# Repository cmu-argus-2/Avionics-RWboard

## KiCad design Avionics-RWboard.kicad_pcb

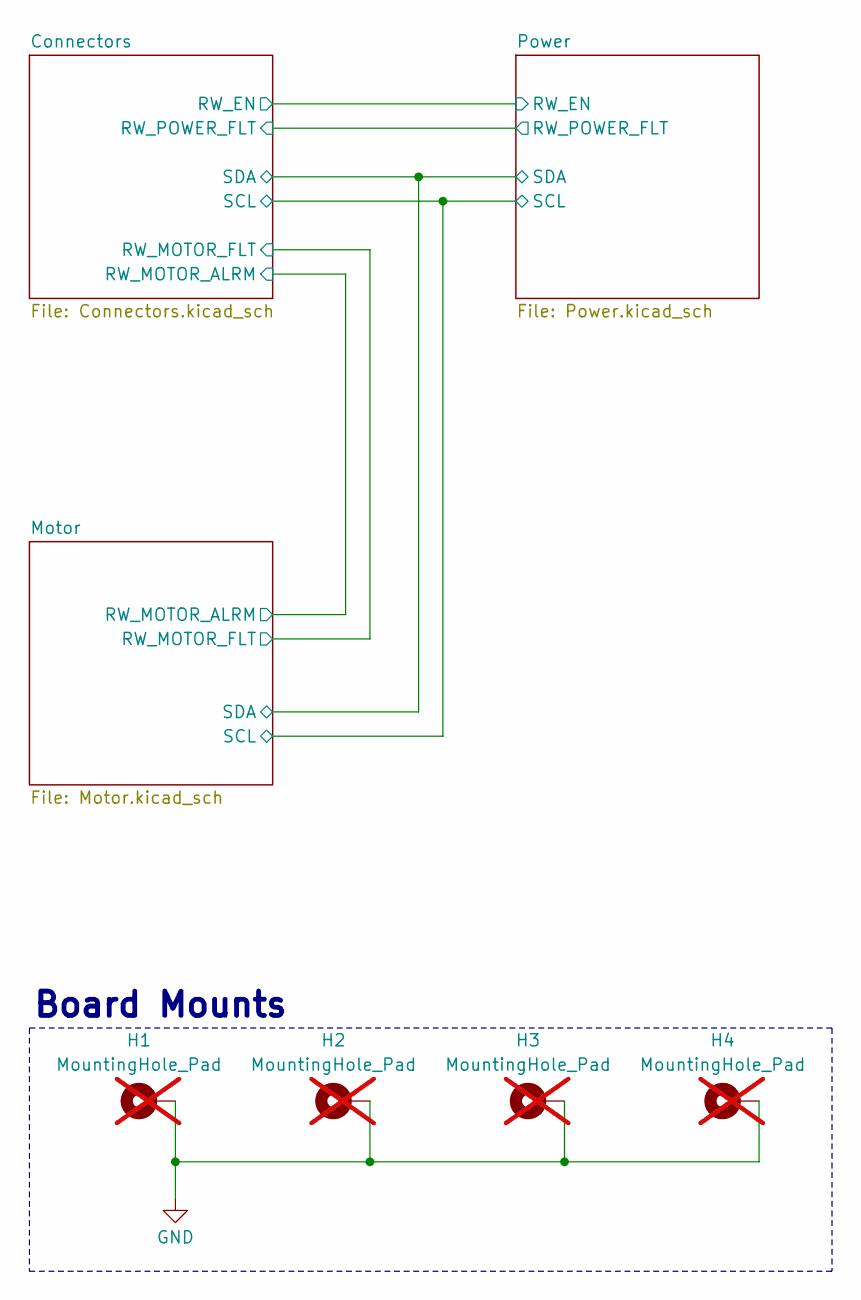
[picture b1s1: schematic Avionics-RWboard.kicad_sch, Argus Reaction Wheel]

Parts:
H1, H2, H3, H4: MountingHole_Pad; MountingHole_3.2mm_M3_Pad_Via; not fitted

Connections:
GND: H1.1, H2.1, H3.1, H4.1; also elsewhere on the board

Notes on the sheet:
Board Mounts

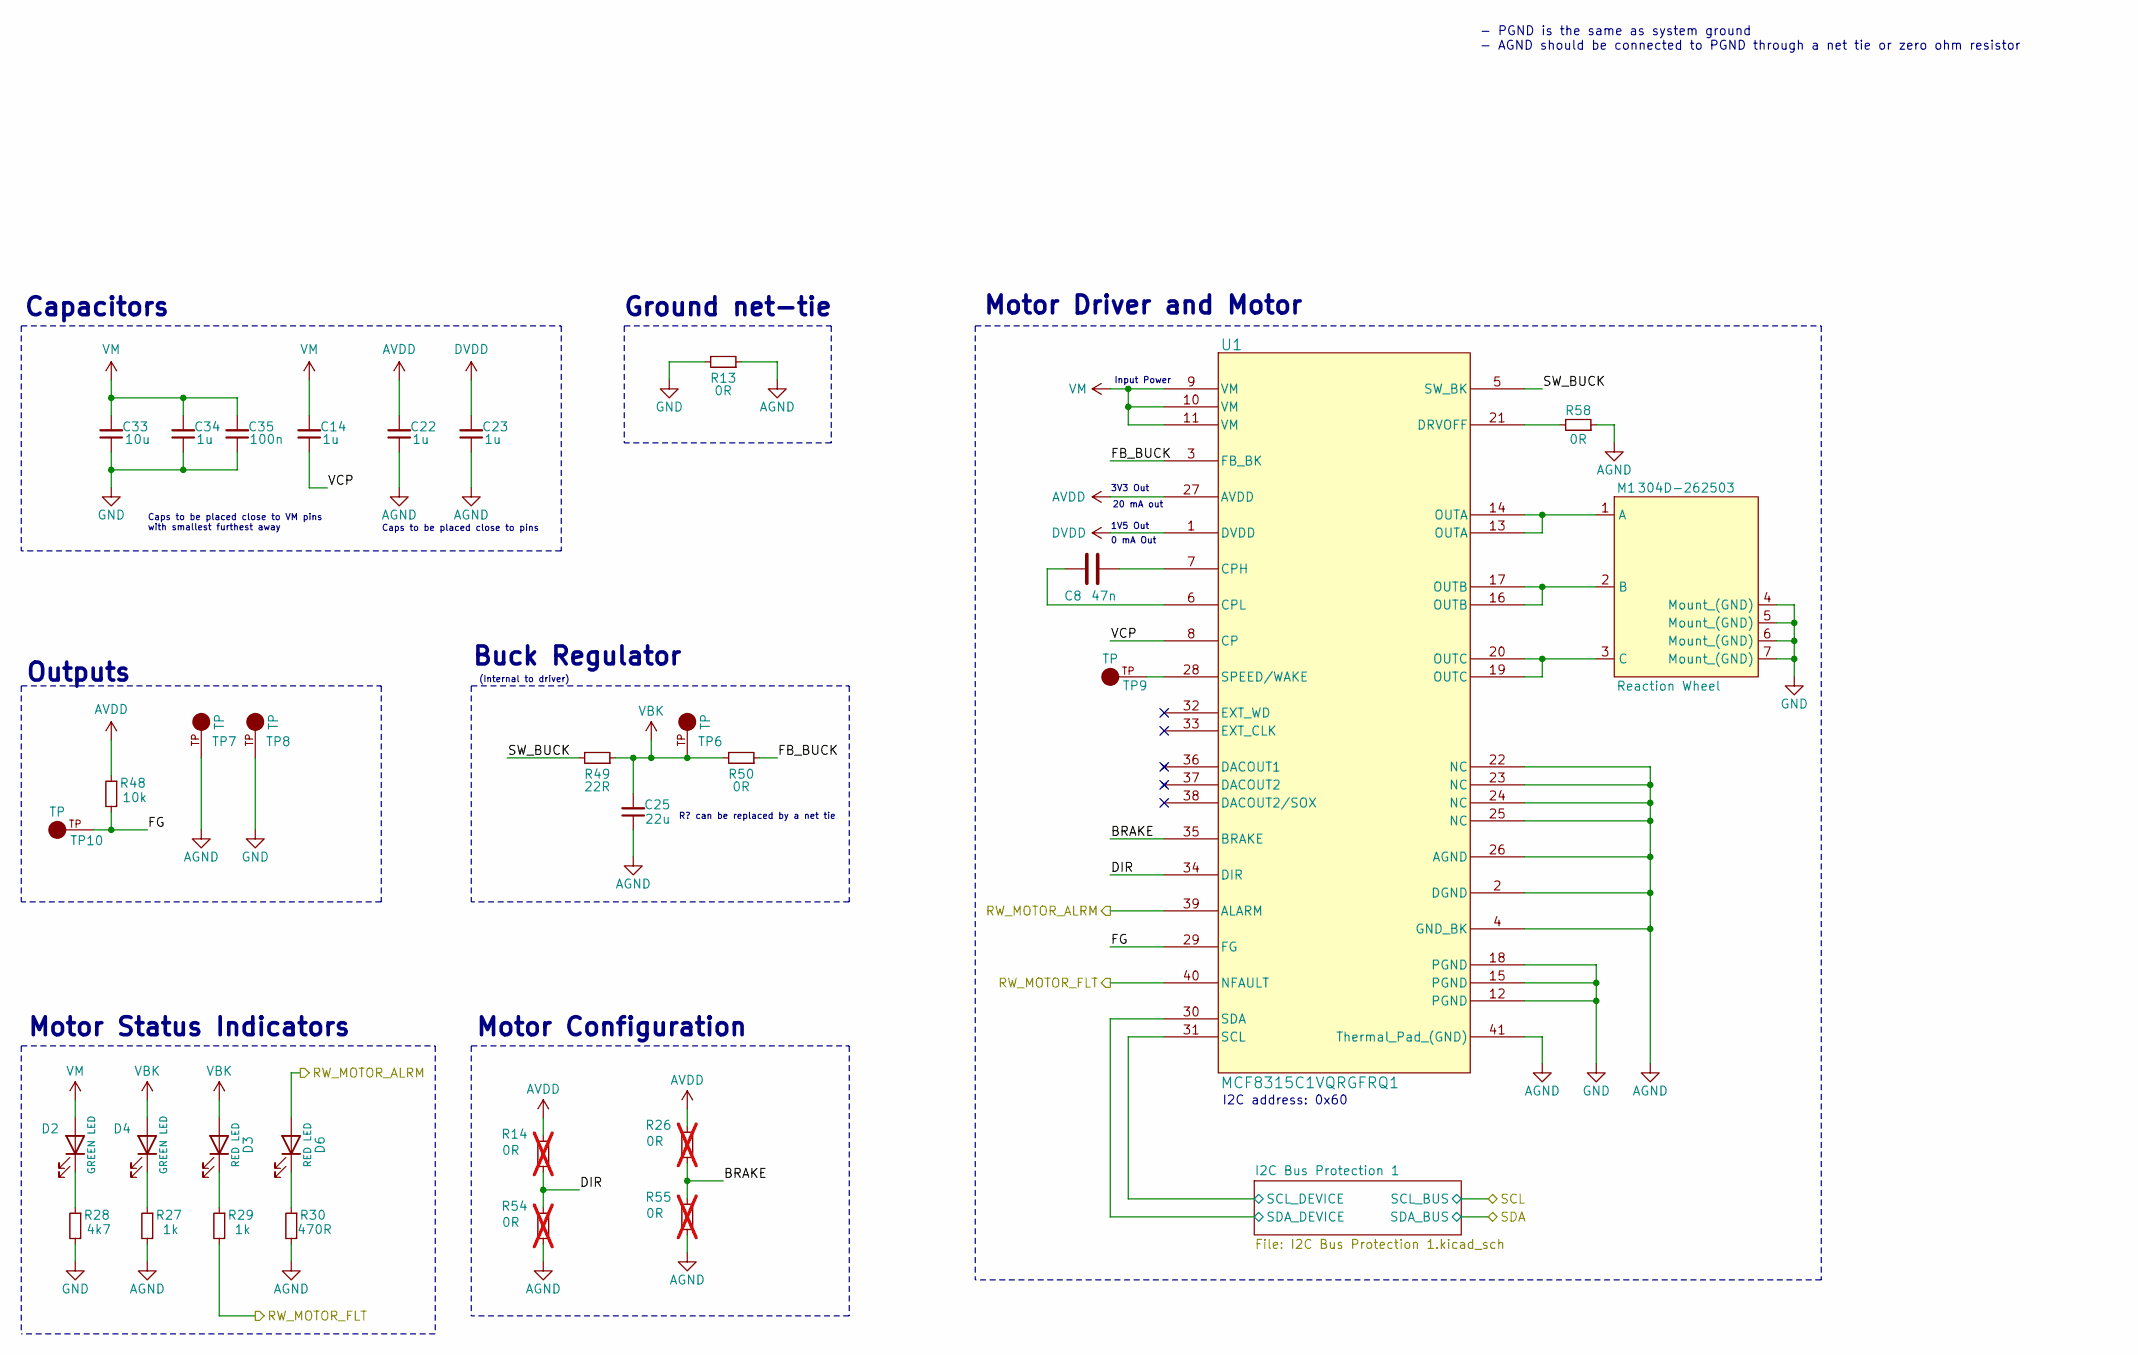
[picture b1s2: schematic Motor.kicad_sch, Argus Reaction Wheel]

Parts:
C8: 47n; C_0603_1608Metric; Part GCM188R71H473KA55D; Digikey PN 490-4934-1-ND
C14, C22, C23, C34: 1u; C_0603_1608Metric; Part CL10B105KA8NNNC; Digikey PN 1276-1184-1-ND
C25: 22u; C_0603_1608Metric; MPN CL10A226MP8NUNE; Digikey PN 1276-1274-1-ND
C33: 10u; C_1206_3216Metric_Pad1.33x1.80mm_HandSolder; Part CL31B106KAHNNNE; Digikey PN 1276-1804-1-ND
C35: 100n; C_0402_1005Metric_Pad0.74x0.62mm_HandSolder; Part C0402C103K3RACTU; Digikey PN 399-C0402C103K3RACTUCT-ND
D2, D4: GREEN LED; LED_0603_1608Metric; Manufacturer_Part_Number LTST-C190KGKT; Digikey PN 1830-1064-1-ND
D3, D6: RED LED; LED_0603_1608Metric; Manufacturer_Part_Number LTST-C190KRKT; Digikey PN 1830-1065-1-ND
M1: 304D-262503; Reaction_Wheel; MPN 304D-262503; Digikey PN 4827-304D-262503CT-ND
R13, R50: 0R; R_0805_2012Metric_Pad1.20x1.40mm_HandSolder; MPN RC0805JR-070RL; Digikey PN 311-0.0ARCT-ND
R14, R26, R54, R55: 0R; R_0402_1005Metric_Pad0.72x0.64mm_HandSolder; MPN RC0402JR-070RL; Digikey PN 311-0.0JRCT-ND; not fitted
R27, R29: 1k; R_0603_1608Metric; MPN RC0603FR-071KL; Digikey PN 311-1.00KHRCT-ND
R28: 4k7; R_0603_1608Metric; MPN RC0603FR-074K7L; Digikey PN 311-4.70KHRCT-ND
R30: 470R; R_0603_1608Metric; MPN RC0603FR-13470RL; Digikey PN 13-RC0603FR-13470RLCT-ND
R48: 10k; R_0603_1608Metric; MPN RC0603FR-0710KL; Digikey PN 311-10.0KHRCT-ND
R49: 22R; R_2512_6332Metric_Pad1.40x3.35mm_HandSolder; Part CRCW251222R0FKEGHP; Digikey PN 541-CRCW251222R0FKEGHPCT-ND
R58: 0R; R_0402_1005Metric_Pad0.72x0.64mm_HandSolder; MPN RC0402JR-070RL; Digikey PN 311-0.0JRCT-ND
TP6, TP7, TP8, TP9, TP10: TP; KEYSTONE_5001; MPN 5001; Digikey PN 36-5001-ND
U1: MCF8315C1VQRGFRQ1; VQFN40_RGF_TEX; MPN MCF8315C1VQRGFRQ1; Digikey PN 296-MCF8315C1VQRGFRQ1CT-ND

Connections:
/Connectors/RW_MOTOR_ALRM: D6.2 (A), U1.39 (ALARM); also elsewhere on the board
/Connectors/RW_MOTOR_FLT: R29.2, U1.40 (NFAULT); also elsewhere on the board
/Motor/BRAKE: R26.1, R55.2, U1.35 (BRAKE)
/Motor/DIR: R14.1, R54.2, U1.34 (DIR)
/Motor/FB_BUCK: R50.1, U1.3 (FB_BK)
/Motor/FG: R48.2, TP10.TP, U1.29 (FG)
/Motor/I2C Bus Protection 1/SCL_DEVICE: U1.31 (SCL); also elsewhere on the board
/Motor/I2C Bus Protection 1/SDA_DEVICE: U1.30 (SDA); also elsewhere on the board
/Motor/SW_BUCK: R49.2, U1.5 (SW_BK)
/Motor/VCP: C14.1, U1.8 (CP)
AGND: C22.1, C23.1, C25.1, R13.1, R27.2, R30.2, R54.1, R55.1, R58.1, TP7.TP, U1.2 (DGND), U1.4 (GND_BK), U1.22 (NC), U1.23 (NC), U1.24 (NC), U1.25 (NC), U1.26 (AGND), U1.41 (Thermal_Pad_(GND))
AVDD: C22.2, R14.2, R26.2, R48.1, U1.27 (AVDD)
DVDD: C23.2, U1.1 (DVDD)
GND: C33.1, C34.1, C35.1, M1.4 (Mount_(GND)), M1.5 (Mount_(GND)), M1.6 (Mount_(GND)), M1.7 (Mount_(GND)), R13.2, R28.2, TP8.TP, U1.12 (PGND), U1.15 (PGND), U1.18 (PGND); also elsewhere on the board
unnamed: D2.1 (K), R28.1
unnamed: D3.1 (K), R29.1
unnamed: D4.1 (K), R27.1
unnamed: D6.1 (K), R30.1
unnamed: M1.1 (A), U1.13 (OUTA), U1.14 (OUTA)
unnamed: M1.2 (B), U1.16 (OUTB), U1.17 (OUTB)
unnamed: M1.3 (C), U1.19 (OUTC), U1.20 (OUTC)
unnamed: C8.1, U1.7 (CPH)
unnamed: C8.2, U1.6 (CPL)
unnamed: R58.2, U1.21 (DRVOFF)
unnamed: TP9.TP, U1.28 (SPEED/WAKE)
VBK: C25.2, D3.2 (A), D4.2 (A), R49.1, R50.2, TP6.TP
VM: C14.2, C33.2, C34.2, C35.2, D2.2 (A), U1.9 (VM), U1.10 (VM), U1.11 (VM); also elsewhere on the board

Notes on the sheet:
20 mA out
3V3 Out
Caps to be placed close to pins
Buck Regulator
0 mA Out
R? can be replaced by a net tie
Input Power
Motor Status Indicators
I2C address: 0x60
Motor Driver and Motor
Caps to be placed close to VM pins with smallest furthest away
Ground net-tie
Outputs
1V5 Out
- PGND is the same as system ground - AGND should be connected to PGND through a net tie or zero ohm resistor
Motor Configuration
(Internal to driver)
Capacitors

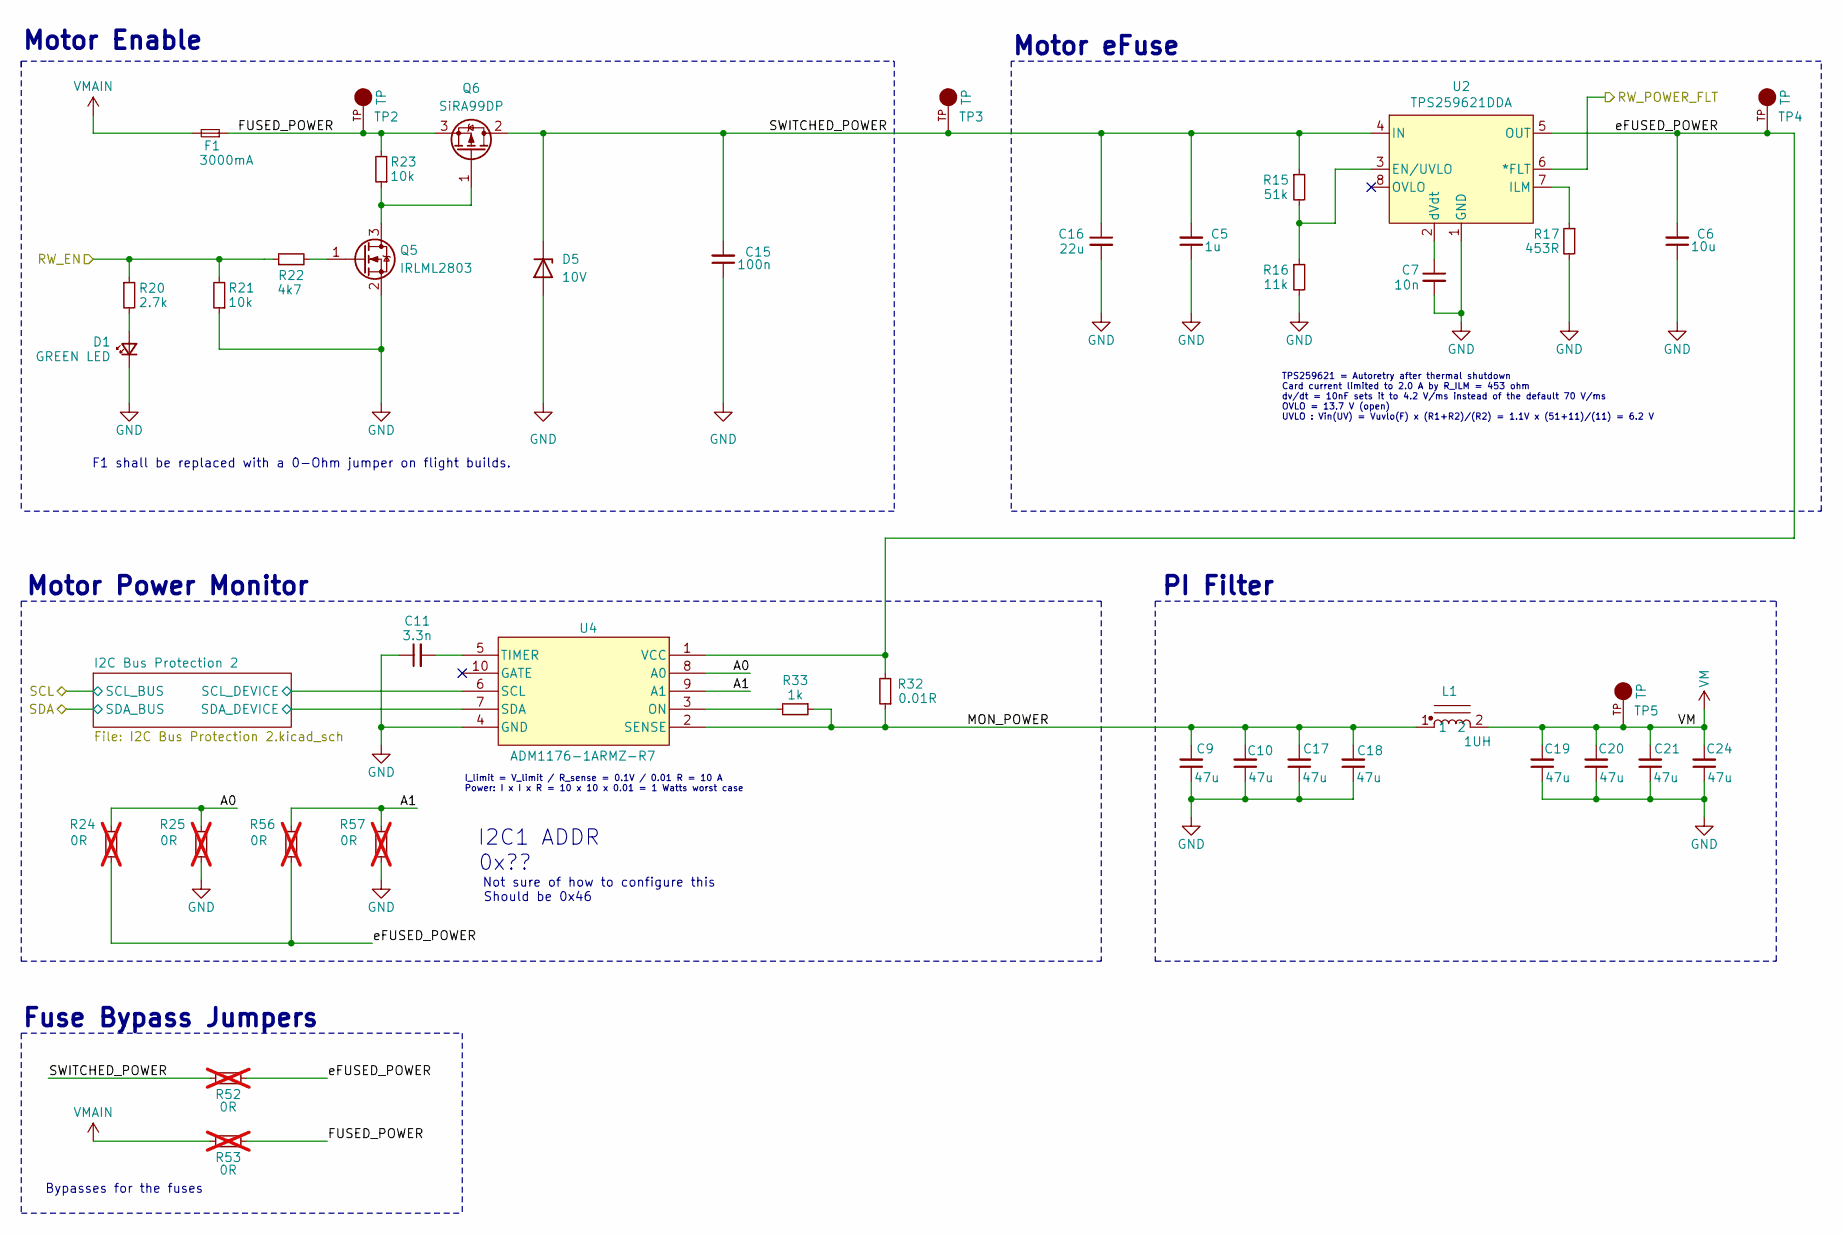
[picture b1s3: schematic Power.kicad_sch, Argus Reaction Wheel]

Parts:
C5: 1u; C_0603_1608Metric; Part CL10B105KA8NNNC; Digikey PN 1276-1184-1-ND
C6: 10u; C_1206_3216Metric_Pad1.33x1.80mm_HandSolder; Part CL31B106KAHNNNE; Digikey PN 1276-1804-1-ND
C7: 10n; C_0603_1608Metric; MPN CL10B103KO8WPNC; Digikey PN 490-4934-1-ND
C9, C10, C17, C18, C19, C20, C21, C24: 47u; C_1206_3216Metric_Pad1.33x1.80mm_HandSolder; Part C3216X5R1E476M160AC; Digikey PN 445-8047-1-ND
C11: 3.3n; C_0603_1608Metric; Part C0603C332K4REC7411; Digikey PN 399-C0603C332K4REC7411CT-ND
C15: 100n; C_0402_1005Metric_Pad0.74x0.62mm_HandSolder; Part C0402C103K3RACTU; Digikey PN 399-C0402C103K3RACTUCT-ND
C16: 22u; C_1210_3225Metric_Pad1.33x2.70mm_HandSolder; MPN GCM32EC71E226KE36K; Digikey PN 490-GCM32EC71E226KE36KCT-ND
D1: GREEN LED; LED_0603_1608Metric; MPN IN-S63AT5A; Digikey PN 1830-1064-1-ND
D5: 10V; Nexperia_DSN1608-2_1.6x0.8mm; MPN PTVS10VZ1USKYL; Digikey PN 1727-2744-1-ND
F1: 3000mA; Fuse_0603_1608Metric; Part SF-0603S300-2; Digikey PN SF-0603S300-2CT-ND
L1: 1UH; HCM1A1104V2; Part HCM1A1104V2-1R0-R; Digikey PN 283-HCM1A1104V2-1R0-RCT-ND
Q5: IRLML2803; SOT-23; MPN IRLML2803TRPBF; Digikey PN IRLML2803PBFCT-ND
Q6: SiRA99DP; PowerPAK SO-8; MPN SIRA99DP-T1-GE3; Digikey PN SIRA99DP-T1-GE3CT-ND
R15: 51k; R_0603_1608Metric; MPN RC0603FR-0751KL; Digikey PN 311-51.0KHRCT-ND
R16: 11k; R_0603_1608Metric; MPN RC0603FR-0711KL; Digikey PN 311-11.0KHRCT-ND
R17: 453R; R_0603_1608Metric; MPN RC0603FR-07453RL; Digikey PN 311-453HRCT-ND
R20: 2.7k; R_0603_1608Metric; MPN CRGCQ0603F2K7; Digikey PN A129693CT-ND
R21, R23: 10k; R_0603_1608Metric; MPN RC0603FR-0710KL; Digikey PN 311-10.0KHRCT-ND
R22: 4k7; R_0603_1608Metric; MPN RC0603FR-074K7L; Digikey PN 311-4.70KHRCT-ND
R24, R25, R56, R57: 0R; R_0402_1005Metric_Pad0.72x0.64mm_HandSolder; MPN RC0402JR-070RL; Digikey PN 311-0.0JRCT-ND; not fitted
R32: 0.01R; R_0805_2012Metric_Pad1.20x1.40mm_HandSolder; Part ERJ-8BWFR010V; Digikey PN P.010AUCT-ND
R33: 1k; R_0603_1608Metric; MPN RC0603FR-071KL; Digikey PN 311-1.00KHRCT-ND
R52, R53: 0R; R_2512_6332Metric_Pad1.40x3.35mm_HandSolder; Part RC2512FK-070RL; Digikey PN 13-RC2512FK-070RLCT-ND; not fitted
TP2, TP3, TP4, TP5: TP; KEYSTONE_5001; MPN 5001; Digikey PN 36-5001-ND
U2: TPS259621DDA; Texas_R-PDSO-G8_EP2.95x4.9mm_Mask2.4x3.1mm_ThermalVias; MPN TPS259620DDAT; Digikey PN 296-TPS259621DDARCT-ND
U4: ADM1176-1ARMZ-R7; MSOP-10_3x3mm_P0.5mm; Manufacturer_Part_Number ADM1176-1ARMZ-R7; Digikey PN 505-ADM1176-1ARMZ-R7CT-ND

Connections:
/Connectors/RW_EN: R20.1, R21.2, R22.1; also elsewhere on the board
/Connectors/RW_POWER_FLT: U2.6 (*FLT); also elsewhere on the board
/Power/A0: R24.2, R25.2, U4.8 (A0)
/Power/A1: R56.2, R57.2, U4.9 (A1)
/Power/FUSED_POWER: F1.1, Q6.3 (S), R23.2, R53.1, TP2.TP
/Power/I2C Bus Protection 2/SCL_DEVICE: U4.6 (SCL); also elsewhere on the board
/Power/I2C Bus Protection 2/SDA_DEVICE: U4.7 (SDA); also elsewhere on the board
/Power/MON_POWER: C9.2, C10.2, C17.2, C18.2, L1.1, R32.1, R33.1, U4.2 (SENSE)
/Power/SWITCHED_POWER: C5.2, C15.2, C16.1, D5.1 (K), Q6.2 (D), R15.1, R52.2, TP3.TP, U2.4 (IN)
/Power/eFUSED_POWER: C6.2, R24.1, R32.2, R52.1, R56.1, TP4.TP, U2.5 (OUT), U4.1 (VCC)
GND: C5.1, C6.1, C7.2, C9.1, C10.1, C11.1, C15.1, C16.2, C17.1, C18.1, C19.1, C20.1, C21.1, C24.1, D1.1 (K), D5.2 (A), Q5.2 (S), R16.2, R17.2, R21.1, R25.1, R57.1, U2.1 (GND), U2.9 (GND), U4.4 (GND); also elsewhere on the board
unnamed: D1.2 (A), R20.2
unnamed: Q5.3 (D), Q6.1 (G), R23.1
unnamed: Q5.1 (G), R22.2
unnamed: R15.2, R16.1, U2.3 (EN/UVLO)
unnamed: R17.1, U2.7 (ILM)
unnamed: C7.1, U2.2 (dVdt)
unnamed: R33.2, U4.3 (ON)
unnamed: C11.2, U4.5 (TIMER)
VM: C19.2, C20.2, C21.2, C24.2, L1.2, TP5.TP; also elsewhere on the board
VMAIN: F1.2, R53.2; also elsewhere on the board

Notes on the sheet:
Not sure of how to configure this
I2C1 ADDR
0x??
Motor Enable
F1 shall be replaced with a 0-Ohm jumper on flight builds.
I_limit = V_limit / R_sense = 0.1V / 0.01 R = 10 A Power: I x I x R = 10 x 10 x 0.01 = 1 Watts worst case
Motor Power Monitor
TPS259621 = Autoretry after thermal shutdown Card current limited to 2.0 A by R_ILM = 453 ohm dv/dt = 10nF sets it to 4.2 V/ms instead of the default 70 V/ms OVLO = 13.7 V (open) UVLO : Vin(UV) = Vuvlo(F) x (R1+R2)/(R2) = 1.1V x (51+11)/(11) = 6.2 V
Fuse Bypass Jumpers
Should be 0x46
PI Filter
Bypasses for the fuses
Motor eFuse

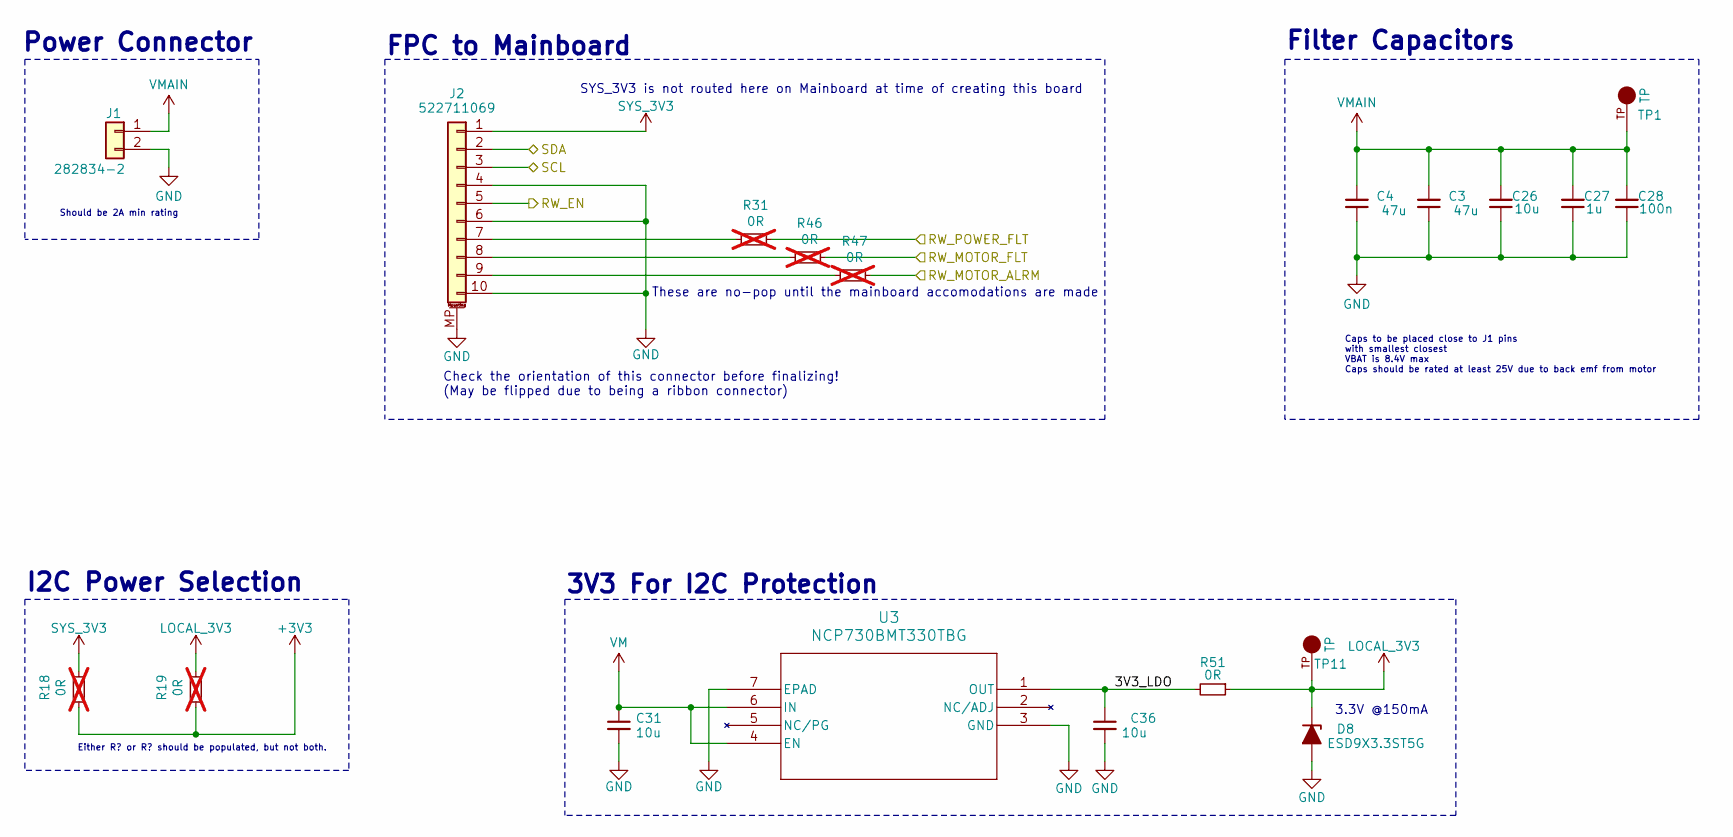
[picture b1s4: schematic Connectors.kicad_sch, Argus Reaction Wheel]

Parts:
C3, C4: 47u; C_1206_3216Metric_Pad1.33x1.80mm_HandSolder; Part C3216X5R1E476M160AC; Digikey PN 445-8047-1-ND
C26: 10u; C_1206_3216Metric_Pad1.33x1.80mm_HandSolder; Part CL31B106KAHNNNE; Digikey PN 1276-1804-1-ND
C27: 1u; C_0603_1608Metric; Part CL10B105KA8NNNC; Digikey PN 1276-1184-1-ND
C28: 100n; C_0402_1005Metric_Pad0.74x0.62mm_HandSolder; Part C0402C103K3RACTU; Digikey PN 399-C0402C103K3RACTUCT-ND
C31, C36: 10u; C_0603_1608Metric; MPN C1608X5R1E106M080AC; Digikey PN 445-9015-1-ND
D8: ESD9X3.3ST5G; D_SOD-923; MPN ESD9X5.0ST5G; Digikey PN ESD9X3.3ST5GOSCT-ND
J1: 282834-2; TE_282834-2; MPN 282834-2; Digikey PN A98333-ND
J2: 522711069; Molex_200528-0100_1x10-1MP_P1.00mm_Horizontal; MPN 200528-0100; Digikey PN 900-2005280100CT-ND
R18, R19, R31, R46, R47: 0R; R_0402_1005Metric_Pad0.72x0.64mm_HandSolder; MPN RC0402JR-070RL; Digikey PN 311-0.0JRCT-ND; not fitted
R51: 0R; R_0603_1608Metric; MPN CR0603-J/-000ELF; Digikey PN CR0603-J/-000ELFCT-ND
TP1, TP11: TP; KEYSTONE_5001; MPN 5001; Digikey PN 36-5001-ND
U3: NCP730BMT330TBG; WDFN6-2x2_511BR_OSI; MPN NCP730BMT330TBG; Digikey PN 488-NCP730BMT330TBGCT-ND

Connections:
+3V3: R18.1, R19.1; also elsewhere on the board
/Connectors/3V3_LDO: C36.1, R51.2, U3.1 (OUT)
/Connectors/RW_EN: J2.5; also elsewhere on the board
/Connectors/RW_MOTOR_ALRM: R47.2; also elsewhere on the board
/Connectors/RW_MOTOR_FLT: R46.2; also elsewhere on the board
/Connectors/RW_POWER_FLT: R31.2; also elsewhere on the board
/Connectors/SCL: J2.3; also elsewhere on the board
/Connectors/SDA: J2.2; also elsewhere on the board
GND: C3.1, C4.1, C26.1, C27.1, C28.1, C31.2, C36.2, D8.2 (A), J1.2, J2.4, J2.6, J2.10, J2.MP (MountPin), U3.3 (GND), U3.7 (EPAD); also elsewhere on the board
LOCAL_3V3: D8.1 (K), R19.2, R51.1, TP11.TP
unnamed: J2.7, R31.1
unnamed: J2.8, R46.1
unnamed: J2.9, R47.1
SYS_3V3: J2.1, R18.2
VM: C31.1, U3.4 (EN), U3.6 (IN); also elsewhere on the board
VMAIN: C3.2, C4.2, C26.2, C27.2, C28.2, J1.1, TP1.TP; also elsewhere on the board

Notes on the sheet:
Filter Capacitors
Caps to be placed close to J1 pins with smallest closest VBAT is 8.4V max Caps should be rated at least 25V due to back emf from motor
3.3V @150mA
These are no-pop until the mainboard accomodations are made
Check the orientation of this connector before finalizing! (May be flipped due to being a ribbon connector)
Either R? or R? should be populated, but not both.
3V3 For I2C Protection
Should be 2A min rating
I2C Power Selection
SYS_3V3 is not routed here on Mainboard at time of creating this board
Power Connector
FPC to Mainboard

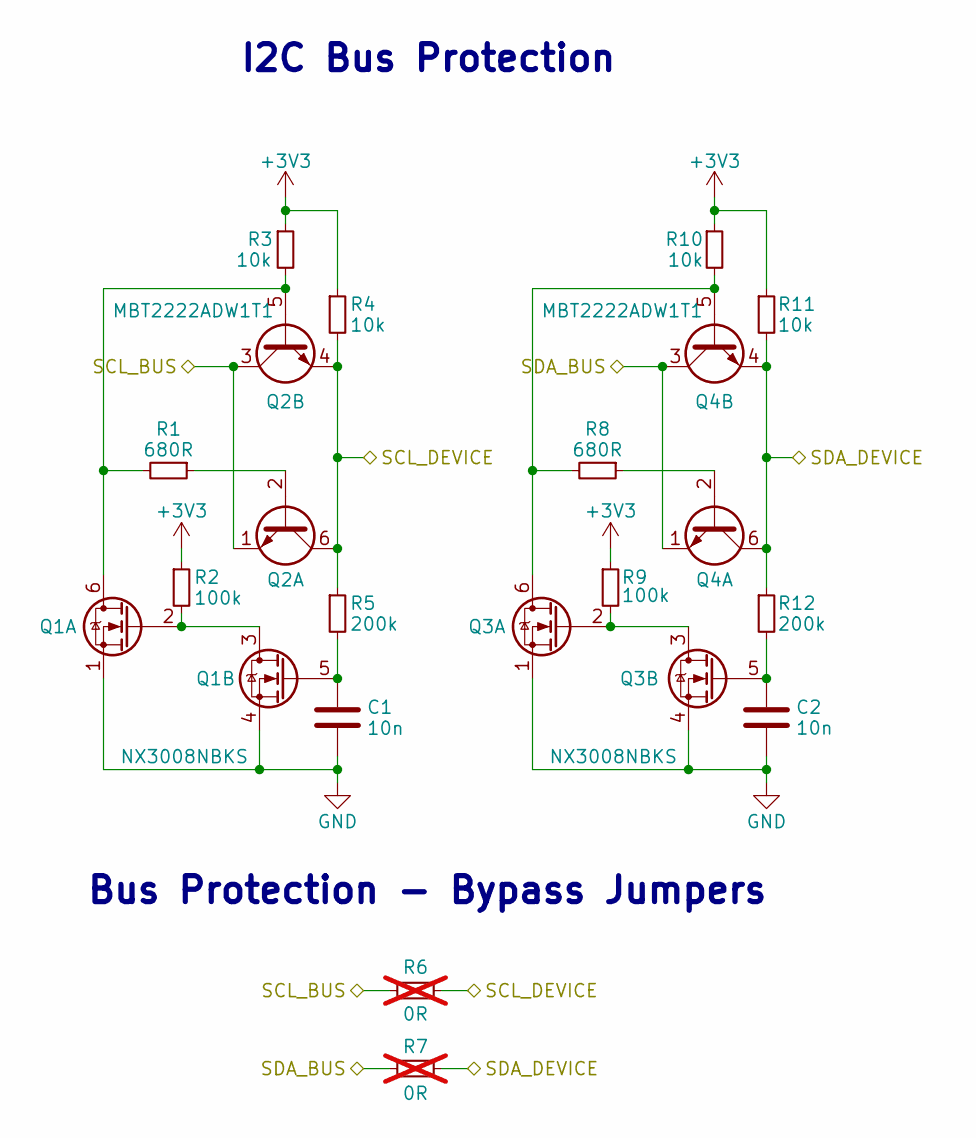
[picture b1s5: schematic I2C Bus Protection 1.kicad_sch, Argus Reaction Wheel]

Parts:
C1, C2: 10n; C_0603_1608Metric; Part CL10B103KO8WPNC; Digikey PN 490-4934-1-ND
Q1, Q3: NX3008NBKS; SOT-363_SC-70-6; Manufacturer_Part_Number NX3008NBKS; Digikey PN 1727-1221-1-ND
Q2, Q4: MBT2222ADW1T1; SOT-363_SC-70-6; Manufacturer_Part_Number MBT2222ADW1T1G; Digikey PN MBT2222ADW1T1GOSCT-ND
R1, R8: 680R; R_0603_1608Metric; MPN RC0603FR-07680RL; Digikey PN 311-680HRCT-ND
R2, R9: 100k; R_0603_1608Metric; MPN RC0603FR-07100KL; Digikey PN 311-100KHRCT-ND
R3, R4, R10, R11: 10k; R_0603_1608Metric; MPN RC0603FR-0710KL; Digikey PN 311-10.0KHRCT-ND
R5, R12: 200k; R_0603_1608Metric; MPN RC0603FR-07200KL; Digikey PN 311-200KHRCT-ND
R6, R7: 0R; R_0603_1608Metric; MPN CR0603-J/-000ELF; Digikey PN CR0603-J/-000ELFCT-ND; not fitted

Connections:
+3V3: R2.1, R3.1, R4.1, R9.1, R10.1, R11.1; also elsewhere on the board
/Connectors/SCL: Q2.1 (E1), Q2.3 (C2), R6.2; also elsewhere on the board
/Connectors/SDA: Q4.1 (E1), Q4.3 (C2), R7.2; also elsewhere on the board
/Motor/I2C Bus Protection 1/SCL_DEVICE: Q2.4 (E2), Q2.6 (C1), R4.2, R5.1, R6.1; also elsewhere on the board
/Motor/I2C Bus Protection 1/SDA_DEVICE: Q4.4 (E2), Q4.6 (C1), R7.1, R11.2, R12.1; also elsewhere on the board
GND: C1.2, C2.2, Q1.1 (S), Q1.4 (S), Q3.1 (S), Q3.4 (S); also elsewhere on the board
unnamed: Q1.6 (D), Q2.5 (B2), R1.2, R3.2
unnamed: Q1.2 (G), Q1.3 (D), R2.2
unnamed: C1.1, Q1.5 (G), R5.2
unnamed: Q2.2 (B1), R1.1
unnamed: Q3.6 (D), Q4.5 (B2), R8.2, R10.2
unnamed: Q3.2 (G), Q3.3 (D), R9.2
unnamed: C2.1, Q3.5 (G), R12.2
unnamed: Q4.2 (B1), R8.1

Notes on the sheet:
Bus Protection - Bypass Jumpers
I2C Bus Protection

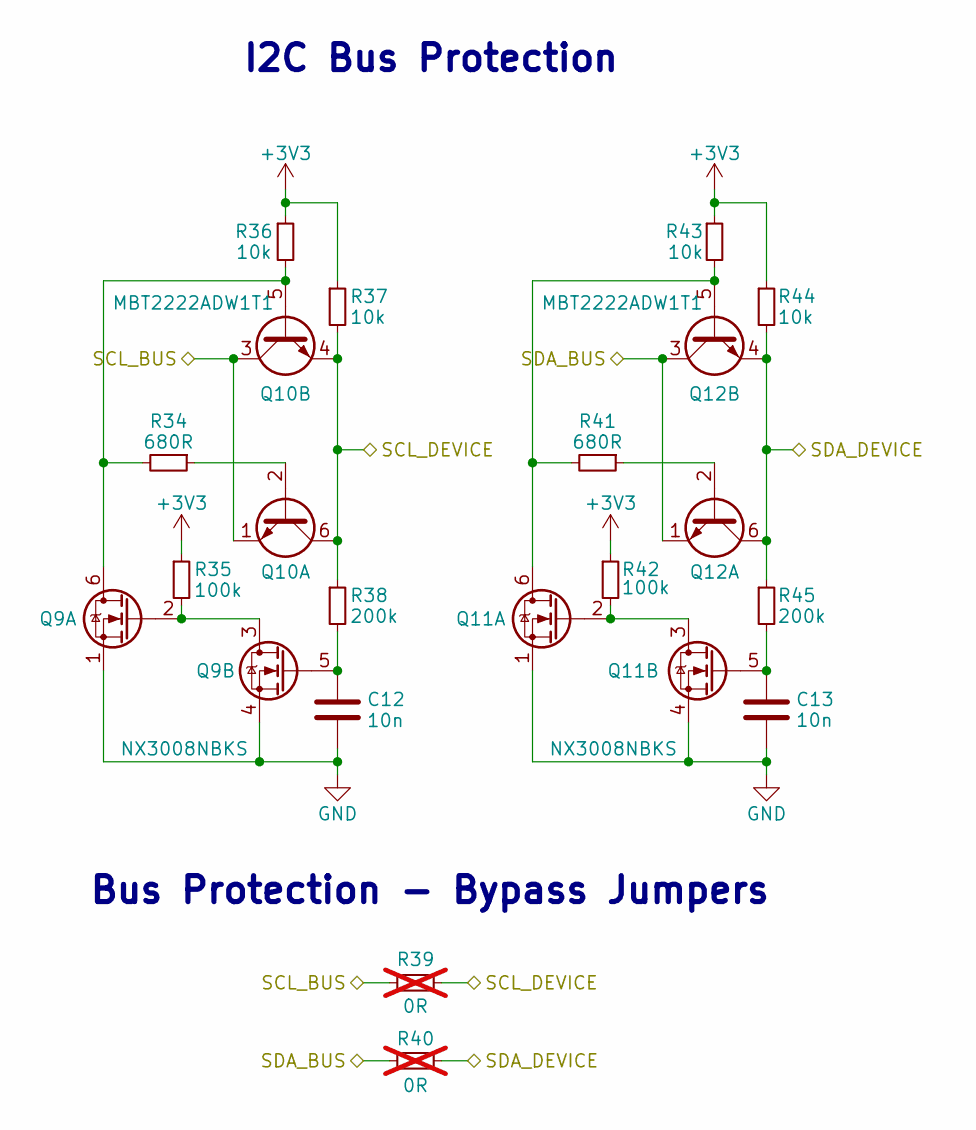
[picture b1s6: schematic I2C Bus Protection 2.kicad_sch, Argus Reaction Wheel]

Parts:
C12, C13: 10n; C_0603_1608Metric; Part CL10B103KO8WPNC; Digikey PN 490-4934-1-ND
Q9, Q11: NX3008NBKS; SOT-363_SC-70-6; Manufacturer_Part_Number NX3008NBKS; Digikey PN 1727-1221-1-ND
Q10, Q12: MBT2222ADW1T1; SOT-363_SC-70-6; Manufacturer_Part_Number MBT2222ADW1T1G; Digikey PN MBT2222ADW1T1GOSCT-ND
R34, R41: 680R; R_0603_1608Metric; MPN RC0603FR-07680RL; Digikey PN 311-680HRCT-ND
R35, R42: 100k; R_0603_1608Metric; MPN RC0603FR-07100KL; Digikey PN 311-100KHRCT-ND
R36, R37, R43, R44: 10k; R_0603_1608Metric; MPN RC0603FR-0710KL; Digikey PN 311-10.0KHRCT-ND
R38, R45: 200k; R_0603_1608Metric; MPN RC0603FR-07200KL; Digikey PN 311-200KHRCT-ND
R39, R40: 0R; R_0603_1608Metric; MPN CR0603-J/-000ELF; Digikey PN CR0603-J/-000ELFCT-ND; not fitted

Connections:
+3V3: R35.1, R36.1, R37.1, R42.1, R43.1, R44.1; also elsewhere on the board
/Connectors/SCL: Q10.1 (E1), Q10.3 (C2), R39.2; also elsewhere on the board
/Connectors/SDA: Q12.1 (E1), Q12.3 (C2), R40.2; also elsewhere on the board
/Power/I2C Bus Protection 2/SCL_DEVICE: Q10.4 (E2), Q10.6 (C1), R37.2, R38.1, R39.1; also elsewhere on the board
/Power/I2C Bus Protection 2/SDA_DEVICE: Q12.4 (E2), Q12.6 (C1), R40.1, R44.2, R45.1; also elsewhere on the board
GND: C12.2, C13.2, Q9.1 (S), Q9.4 (S), Q11.1 (S), Q11.4 (S); also elsewhere on the board
unnamed: Q9.2 (G), Q9.3 (D), R35.2
unnamed: C12.1, Q9.5 (G), R38.2
unnamed: Q10.2 (B1), R34.1
unnamed: Q9.6 (D), Q10.5 (B2), R34.2, R36.2
unnamed: Q11.6 (D), Q12.5 (B2), R41.2, R43.2
unnamed: Q11.2 (G), Q11.3 (D), R42.2
unnamed: C13.1, Q11.5 (G), R45.2
unnamed: Q12.2 (B1), R41.1

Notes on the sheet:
Bus Protection - Bypass Jumpers
I2C Bus Protection

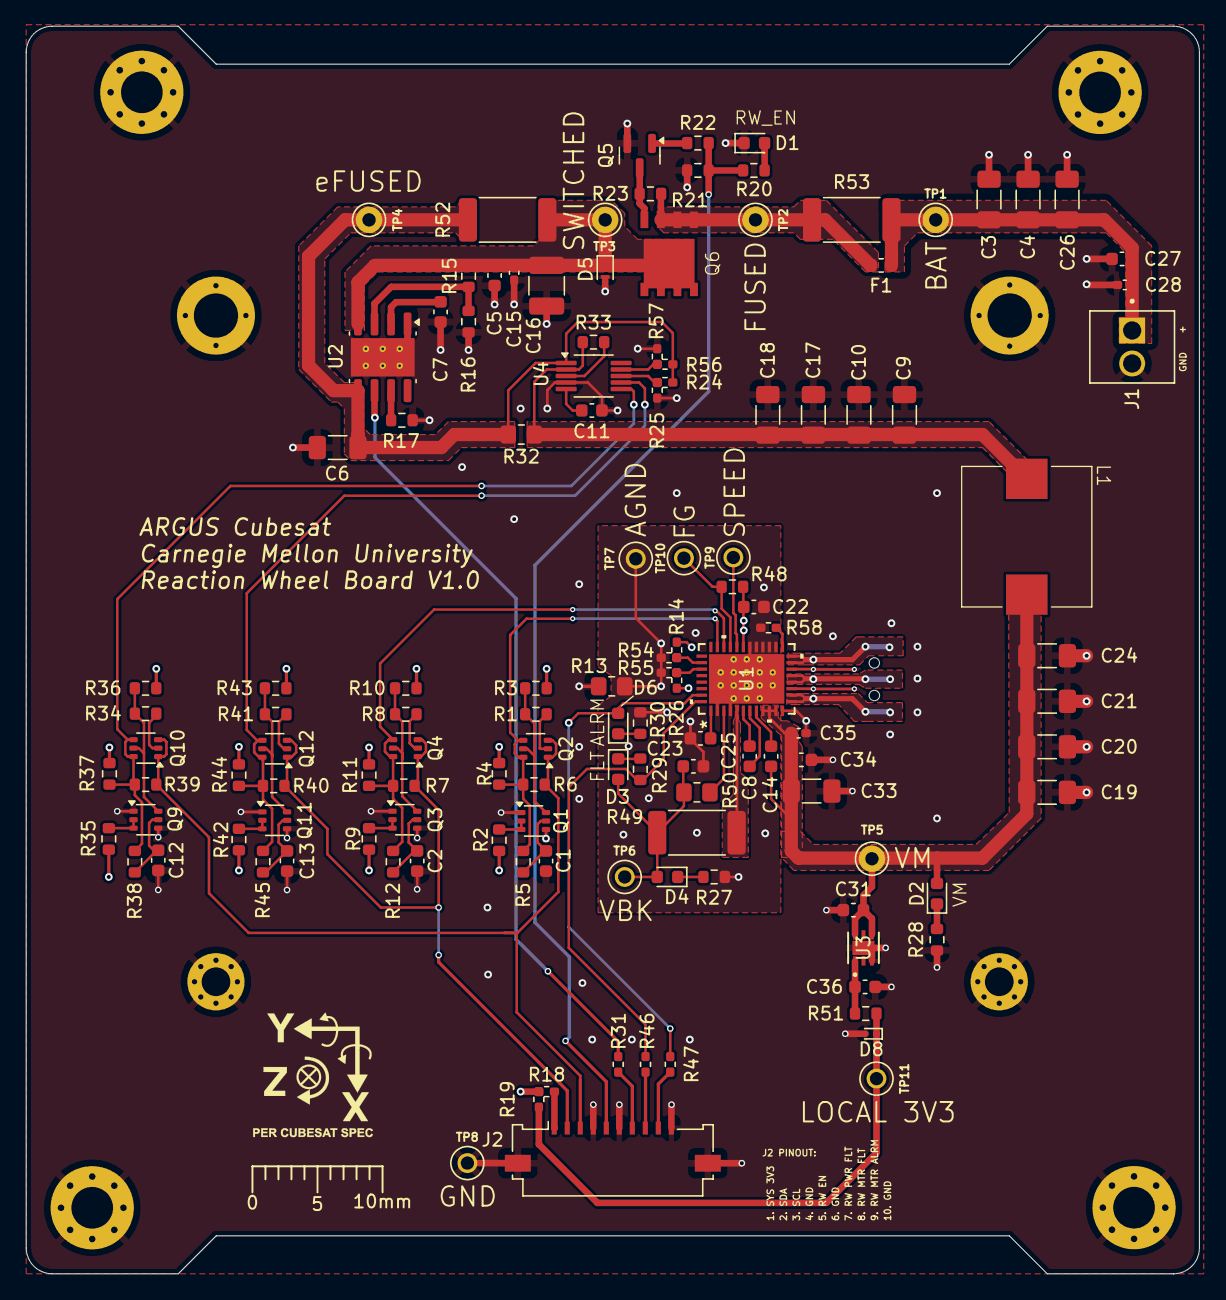
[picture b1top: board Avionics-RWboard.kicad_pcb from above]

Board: 4 copper layers, 90.1 x 95.9 mm, 132 parts (1 on the bottom side), 71 nets.

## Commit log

2025-02-22 Upload .gitignore
2025-02-22 Upload files
2025-03-15 Add schematics. Still need to check power and voltage ratings. Still need to get all the footprints sorted out. Still need to layout board.
2025-03-15 Checked all power and voltage ratings and corrected where needed. Still need footprints and layout completed.
2025-03-15 Clean notes
2025-03-15 Start layout, still missing some footprints
2025-03-15 Add more test points
2025-03-25 Layout mostly complete
2025-03-25 Update silkscreen
2025-03-25 Push changes that were not saved on the schematic with last push
2025-03-28 Push requested changes - silkscreen, copper width, pi filter
2025-04-09 Add and correct BOM for easy Digikey ordering
2026-01-21 Local Stash

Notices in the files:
parts and their libraries:
License: Apache-2.0
